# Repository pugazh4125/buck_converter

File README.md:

# buck_converter

This project is a 12V to 6V DC-DC buck converter. I first simulated it in MATLAB and then designed the PCB for potential hardware implementation.

After learning about DC-DC converters in class (buck, boost, buck-boost), I wanted to design a buck converter myself. I also needed a buck converter for a project I’m working on, so this was a perfect opportunity.

While designing this converter, I learned a lot of practical concepts that aren’t covered in class, and it helped me understand the theoretical concepts much better.  

 - Copy.png)

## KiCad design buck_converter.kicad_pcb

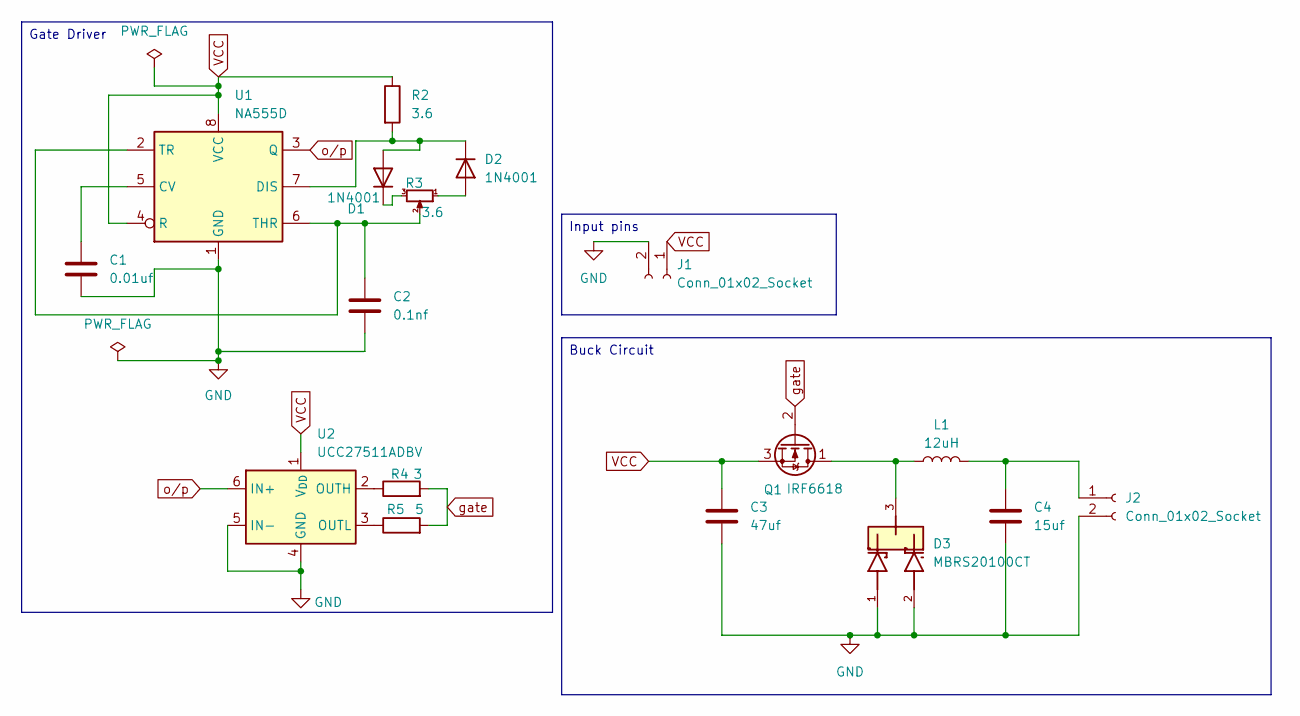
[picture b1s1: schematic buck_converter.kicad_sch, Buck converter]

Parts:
C1: 0.01uf; C_1206_3216Metric
C2: 0.1nf; C_1206_3216Metric
C3: 47uf; C_1206_3216Metric
C4: 15uf; C_1206_3216Metric
D1, D2: 1N4001; D_DO-41_SOD81_P10.16mm_Horizontal
D3: MBRS20100CT; DIO_MBRS20100CT; PARTREV M2103
J1, J2: Conn_01x02_Socket; PinHeader_1x02_P2.54mm_Vertical_SMD_Pin1Right
L1: 12uH; L_Wurth_WE-LQSH-4020
Q1: IRF6618; DirectFET_MT
R2: 3.6; R_0603_1608Metric
R3: 3.6; Potentiometer_Bourns_3266X_Horizontal
R4: 3; R_0603_1608Metric
R5: 5; R_0603_1608Metric
U1: NA555D; SOIC-8_3.9x4.9mm_P1.27mm
U2: UCC27511ADBV; SOT-23-6

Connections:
GND: C1.2, C2.2, C3.2, C4.2, D3.1, D3.2, J1.2, J2.2, U1.1 (GND), U2.4 (GND), U2.5 (IN-)
unnamed: D1.2 (A), D2.1 (K), R2.2, U1.7 (DIS)
unnamed: D1.1 (K), R3.3
unnamed: D2.2 (A), R3.1
unnamed: C4.1, J2.1, L1.2
unnamed: D3.3, L1.1, Q1.1 (D)
unnamed: C1.1, U1.5 (CV)
unnamed: C2.1, R3.2, U1.2 (TR), U1.6 (THR)
unnamed: R4.1, U2.2 (OUTH)
unnamed: R5.1, U2.3 (OUTL)
VCC: C3.1, J1.1, Q1.3 (S), R2.1, U1.4 (R), U1.8 (VCC), U2.1 (V_{DD})
gate: Q1.2 (G), R4.2, R5.2
o/p: U1.3 (Q), U2.6 (IN+)

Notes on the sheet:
Gate Driver
Buck Circuit
Input pins

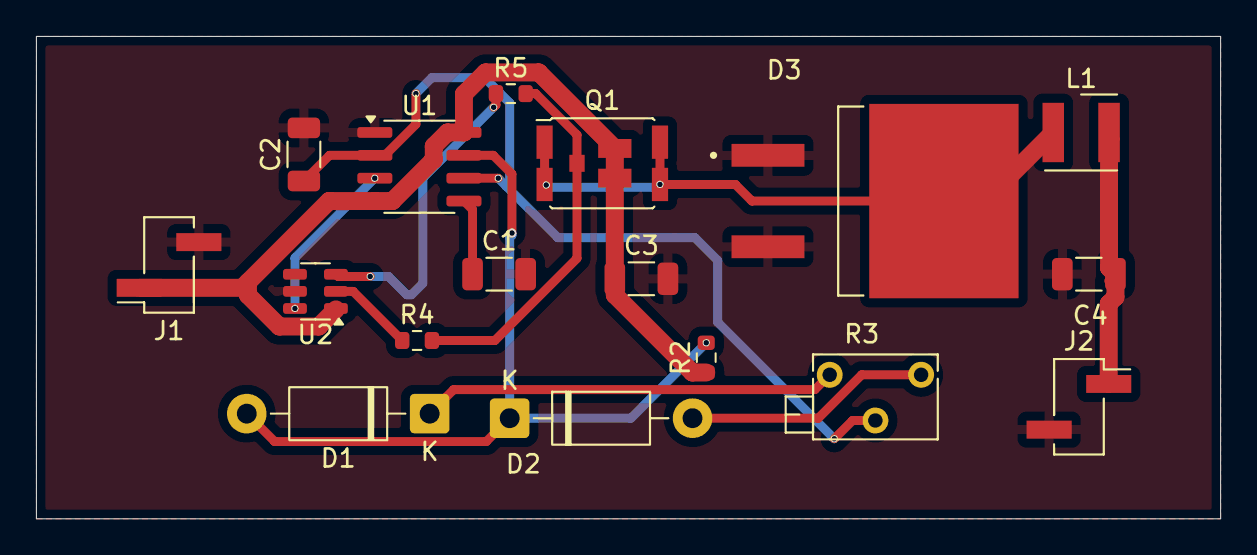
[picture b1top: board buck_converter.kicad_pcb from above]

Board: 2 copper layers, 65.8 x 26.8 mm, 17 parts (0 on the bottom side), 13 nets.
